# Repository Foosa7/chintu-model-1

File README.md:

# chintu-model-1

Clone of [Wagiminator
CH32V003-GameConsole](https://github.com/wagiminator/CH32V003-GameConsole?tab=readme-ov-file) designed to work with lipo battery.

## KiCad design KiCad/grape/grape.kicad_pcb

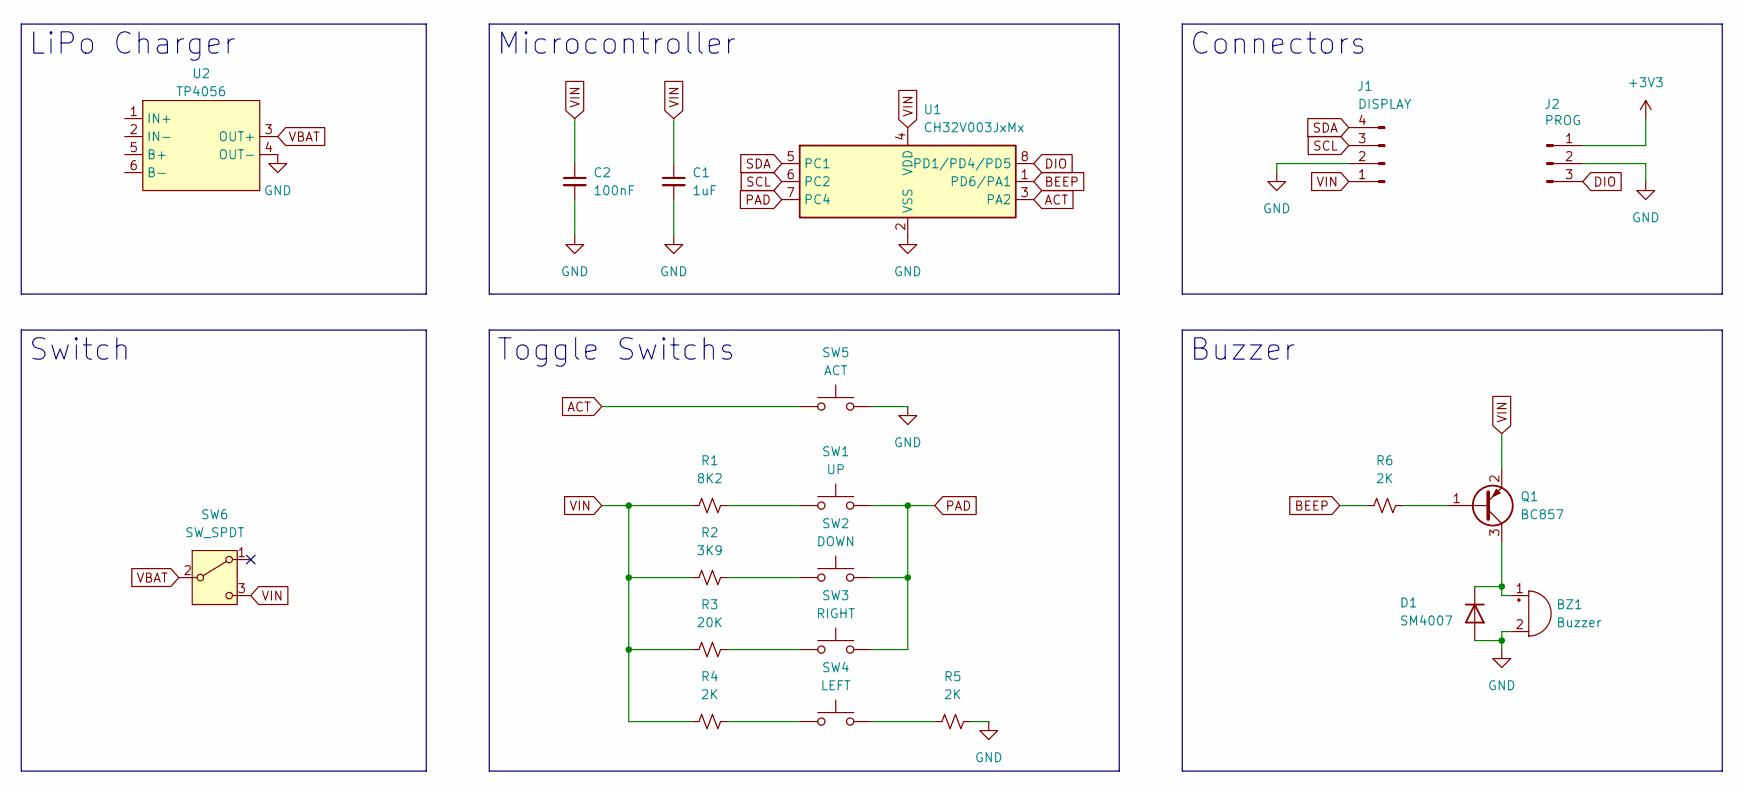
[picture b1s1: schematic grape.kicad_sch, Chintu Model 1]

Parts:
BZ1: Buzzer; MLT-5030
C1: 1uF; C_0603_1608Metric
C2: 100nF; C_0603_1608Metric
D1: SM4007; D_MELF
J1: DISPLAY; SH1106
J2: PROG; PinHeader_1x03_P2.54mm_Vertical
Q1: BC857; SOT-23
R1: 8K2; R_0603_1608Metric
R2: 3K9; R_0603_1608Metric
R3: 20K; R_0603_1608Metric
R4, R5, R6: 2K; R_0603_1608Metric
SW1: UP; SW_SPST_PTS645
SW2: DOWN; SW_SPST_PTS645
SW3: RIGHT; SW_SPST_PTS645
SW4: LEFT; SW_SPST_PTS645
SW5: ACT; SW_SPST_PTS645
SW6: SW_SPDT; SW_SPDT_PCM12
U1: CH32V003JxMx; SOP-8_3.9x4.9mm_P1.27mm
U2: TP4056; TP4056-Module

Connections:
+3V3: J2.1
ACT: SW5.1, U1.3 (PA2)
BEEP: R6.1, U1.1 (PD6/PA1)
DIO: J2.3, U1.8 (PD1/PD4/PD5)
GND: BZ1.2 (-), C1.2, C2.2, D1.2 (A), J1.2, J2.2, R5.2, SW5.2, U1.2 (VSS), U2.4 (OUT-)
unnamed: BZ1.1 (+), D1.1 (K), Q1.3 (C)
unnamed: Q1.1 (B), R6.2
unnamed: R1.2, SW1.1
unnamed: R2.2, SW2.1
unnamed: R3.2, SW3.1
unnamed: R4.2, SW4.1
unnamed: R5.1, SW4.2
PAD: SW1.2, SW2.2, SW3.2, U1.7 (PC4)
SCL: J1.3, U1.6 (PC2)
SDA: J1.4, U1.5 (PC1)
VBAT: SW6.2 (B), U2.3 (OUT+)
VIN: C1.1, C2.1, J1.1, Q1.2 (E), R1.1, R2.1, R3.1, R4.1, SW6.3 (C), U1.4 (VDD)

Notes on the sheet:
Connectors
Switch
LiPo Charger
Buzzer
Toggle Switchs
Microcontroller

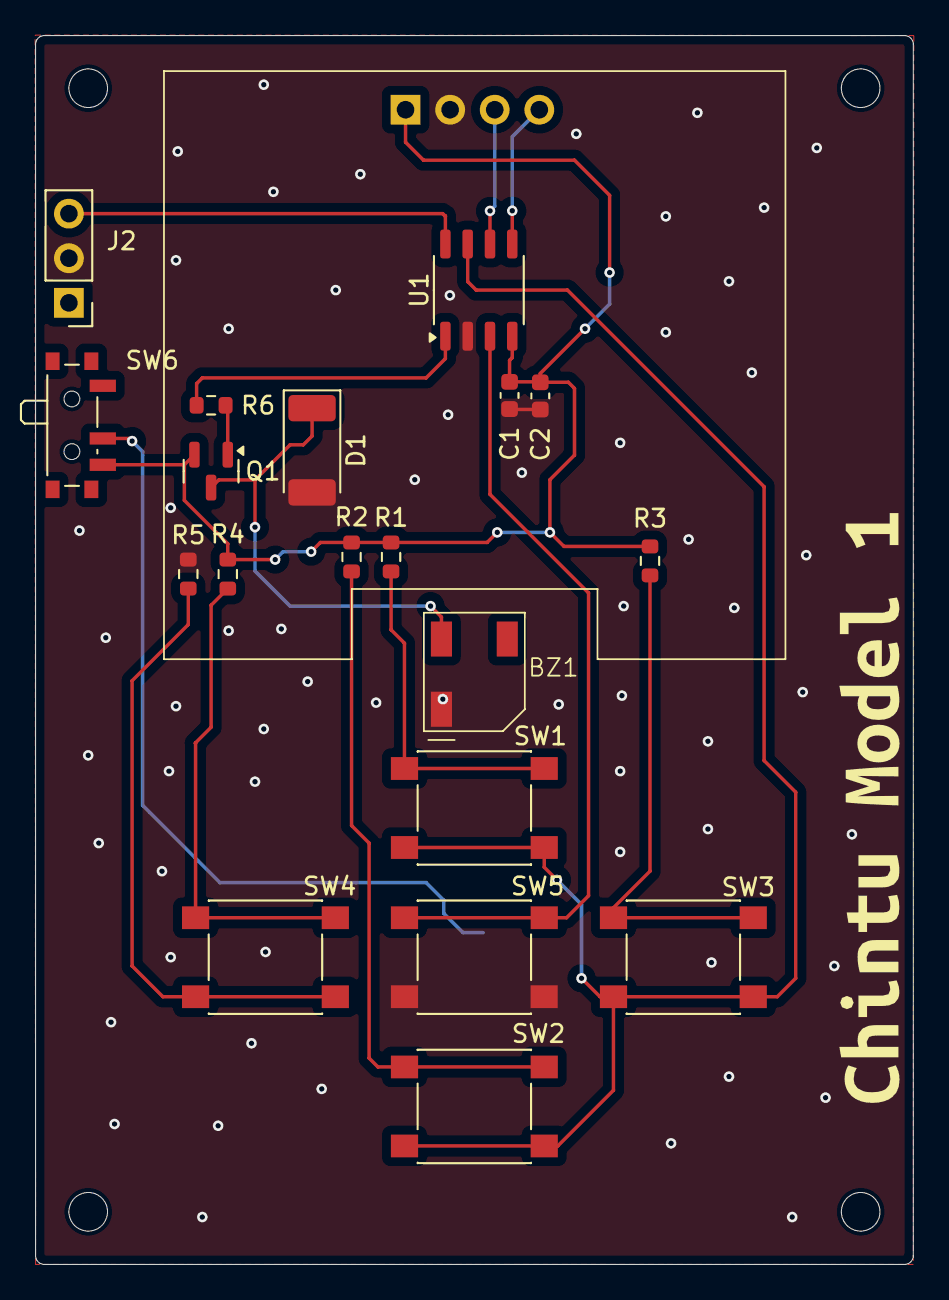
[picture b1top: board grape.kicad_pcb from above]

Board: 2 copper layers, 50.0 x 70.0 mm, 22 parts (1 on the bottom side), 16 nets.

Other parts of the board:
kibuzzard-67E9313F: G***; kibuzzard-67E9313F

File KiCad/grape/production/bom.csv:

Designator,Footprint,Quantity,Value,LCSC Part #
BZ1,MLT-5030,1,Buzzer,
C1,0603,1,1uF,
C2,0603,1,100nF,
D1,D_MELF,1,SM4007,
J1,SH1106,1,DISPLAY,
J2,PinHeader_1x03_P2.54mm_Vertical,1,PROG,
Q1,SOT-23,1,BC857,
R1,0603,1,8K2,
R2,0603,1,3K9,
R3,0603,1,20K,
"R4, R5, R6",0603,3,2K,
SW1,SW_SPST_PTS645,1,UP,
SW2,SW_SPST_PTS645,1,DOWN,
SW3,SW_SPST_PTS645,1,RIGHT,
SW4,SW_SPST_PTS645,1,LEFT,
SW5,SW_SPST_PTS645,1,ACT,
SW6,SW_SPDT_PCM12,1,SW_SPDT,
U1,SOP-8_3.9x4.9mm_P1.27mm,1,CH32V003JxMx,
U2,TP4056-Module,1,TP4056,
